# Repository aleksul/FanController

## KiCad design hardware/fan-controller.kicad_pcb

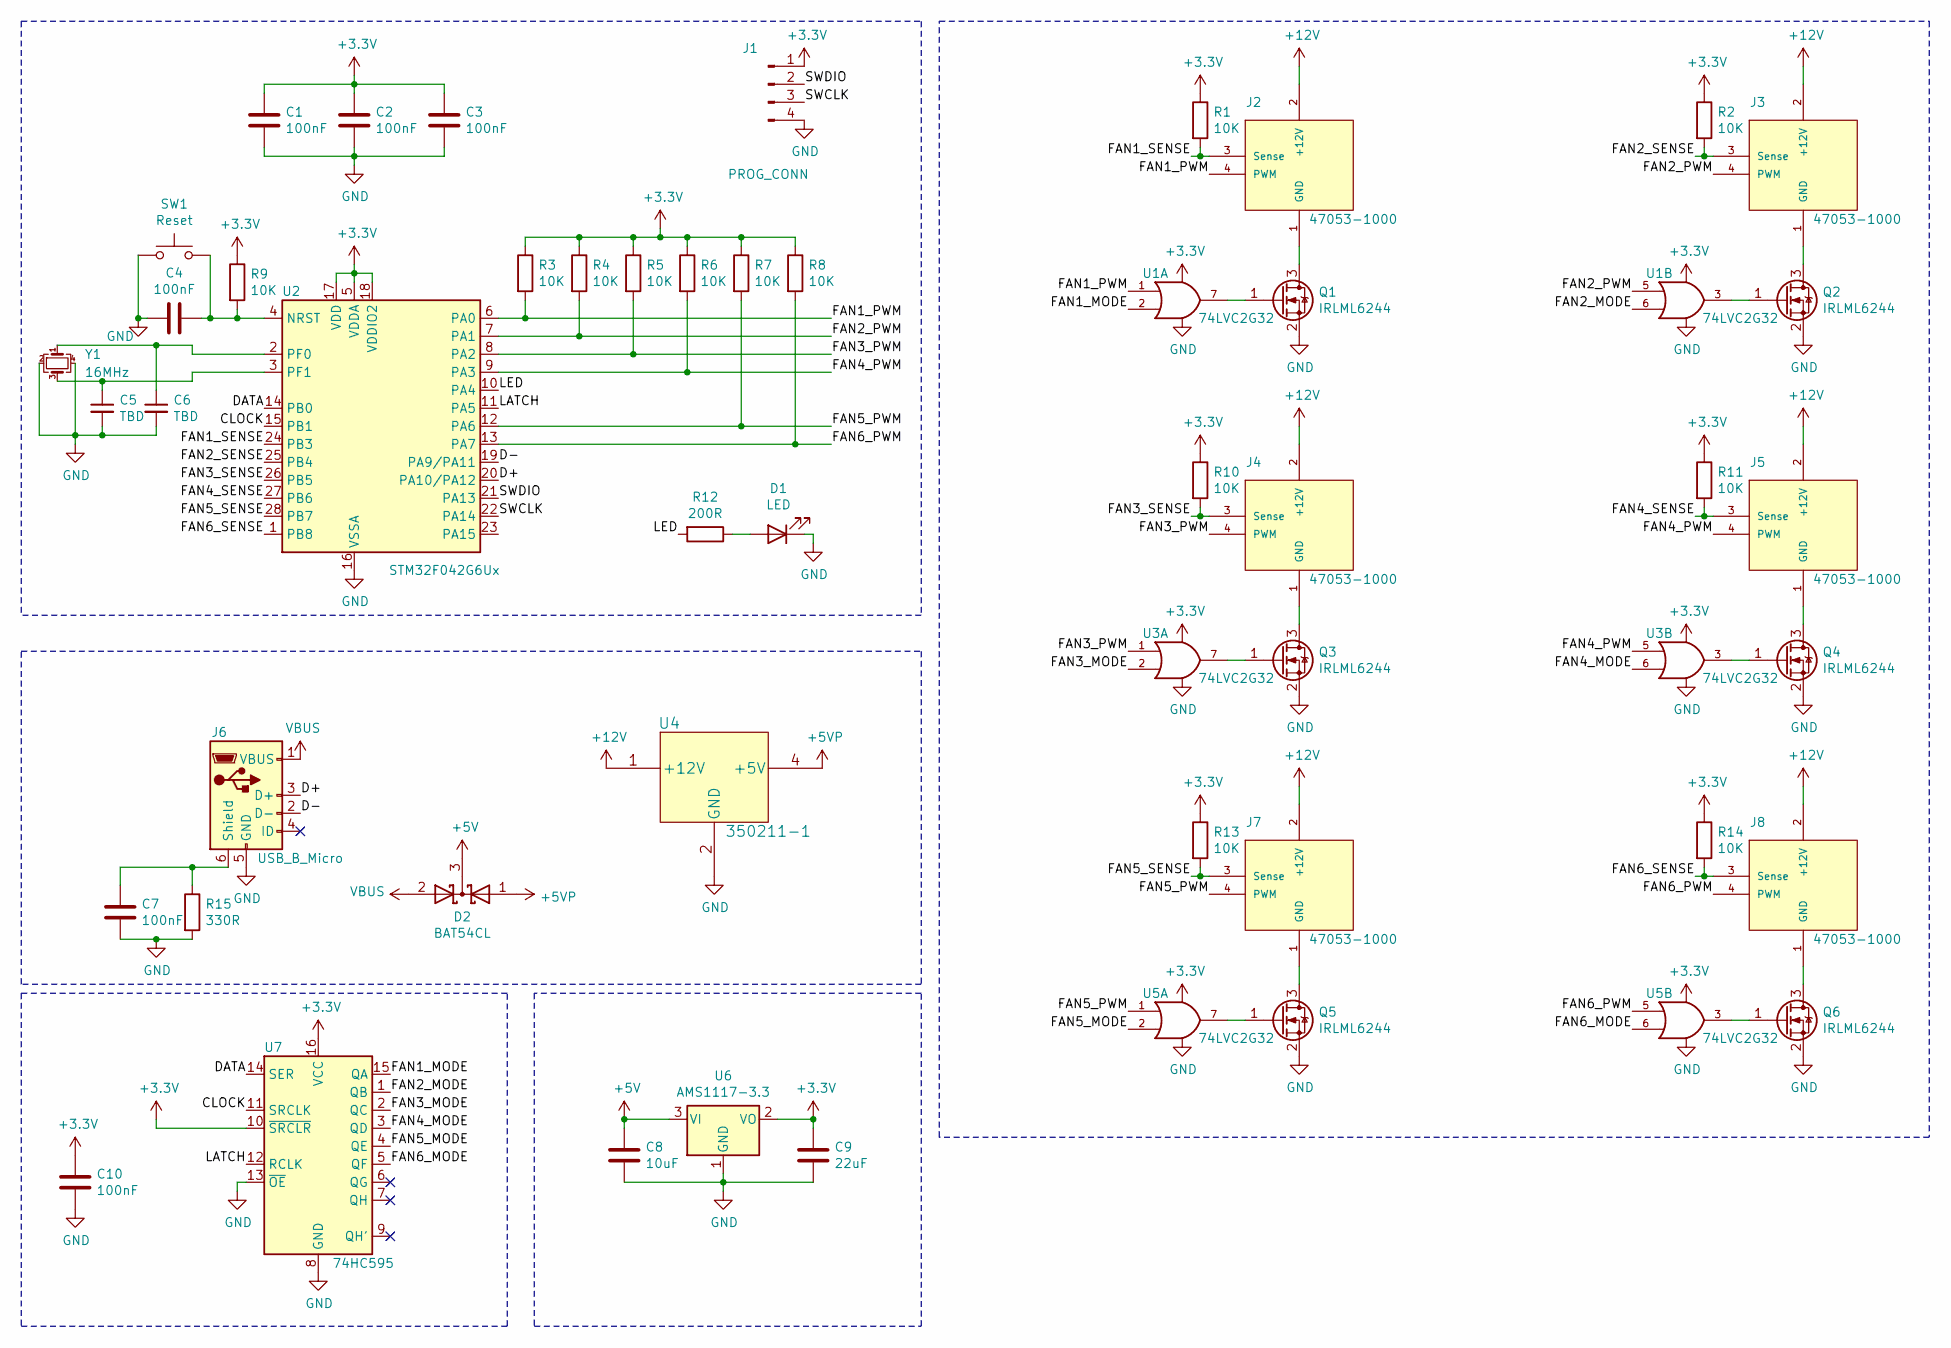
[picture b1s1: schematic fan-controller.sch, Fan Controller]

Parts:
C1, C2, C3, C4, C7, C10: 100nF; C_0805_2012Metric_Pad1.18x1.45mm_HandSolder
C5, C6: TBD; C_0805_2012Metric_Pad1.18x1.45mm_HandSolder
C8: 10uF; C_1206_3216Metric_Pad1.33x1.80mm_HandSolder
C9: 22uF; C_1206_3216Metric_Pad1.33x1.80mm_HandSolder
D1: LED; LED_1206_3216Metric_Pad1.42x1.75mm_HandSolder
D2: BAT54CL; SOT-23_Handsoldering
J1: PROG_CONN; PinHeader_1x04_P2.54mm_Vertical
J2, J3, J4, J5, J7, J8: 47053-1000; 470531000
J6: USB_B_Micro; USB_Micro-B_Molex-105017-0001
Q1, Q2, Q3, Q4, Q5, Q6: IRLML6244; SOT-23_Handsoldering
R1, R2, R3, R4, R5, R6, R7, R8, R9, R10, R11, R13, R14: 10K; R_0805_2012Metric_Pad1.20x1.40mm_HandSolder
R12: 200R; R_0805_2012Metric_Pad1.20x1.40mm_HandSolder
R15: 330R; R_0805_2012Metric_Pad1.20x1.40mm_HandSolder
SW1: Reset; SW_TS-1187A-B-A-B
U1, U3, U5: 74LVC2G32; VSSOP-8_2.3x2mm_P0.5mm
U2: STM32F042G6Ux; QFN-28_4x4mm_P0.5mm
U4: 350211-1
U6: AMS1117-3.3; SOT-223-3_TabPin2
U7: 74HC595; SOIC-16_3.9x9.9mm_P1.27mm
Y1: 16MHz; Crystal_SMD_2520-4Pin_2.5x2.0mm

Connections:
+3V3: C1.1, C2.1, C3.1, C9.1, C10.1, J1.1, R1.1, R2.1, R3.1, R4.1, R5.1, R6.1, R7.1, R8.1, R9.1, R10.1, R11.1, R13.1, R14.1, U1.8 (VCC), U2.5 (VDDA), U2.17 (VDD), U2.18 (VDDIO2), U3.8 (VCC), U5.8 (VCC), U6.2 (VO), U7.10 (~SRCLR), U7.16 (VCC)
+5V: C8.1, D2.3 (K), U6.3 (VI)
+5VP: D2.1 (A), U4.4 (+5V)
+12V: J2.2 (+12V), J3.2 (+12V), J4.2 (+12V), J5.2 (+12V), J7.2 (+12V), J8.2 (+12V), U4.1 (+12V)
/CLOCK: U2.15 (PB1), U7.11 (SRCLK)
/D+: J6.3 (D+), U2.20 (PA10/PA12)
/D-: J6.2 (D-), U2.19 (PA9/PA11)
/DATA: U2.14 (PB0), U7.14 (SER)
/FAN1_MODE: U1.2, U7.15 (QA)
/FAN1_PWM: J2.4 (PWM), R3.2, U1.1, U2.6 (PA0)
/FAN1_SENSE: J2.3 (Sense), R1.2, U2.24 (PB3)
/FAN2_MODE: U1.6, U7.1 (QB)
/FAN2_PWM: J3.4 (PWM), R4.2, U1.5, U2.7 (PA1)
/FAN2_SENSE: J3.3 (Sense), R2.2, U2.25 (PB4)
/FAN3_MODE: U3.2, U7.2 (QC)
/FAN3_PWM: J4.4 (PWM), R5.2, U2.8 (PA2), U3.1
/FAN3_SENSE: J4.3 (Sense), R10.2, U2.26 (PB5)
/FAN4_MODE: U3.6, U7.3 (QD)
/FAN4_PWM: J5.4 (PWM), R6.2, U2.9 (PA3), U3.5
/FAN4_SENSE: J5.3 (Sense), R11.2, U2.27 (PB6)
/FAN5_MODE: U5.2, U7.4 (QE)
/FAN5_PWM: J7.4 (PWM), R7.2, U2.12 (PA6), U5.1
/FAN5_SENSE: J7.3 (Sense), R13.2, U2.28 (PB7)
/FAN6_MODE: U5.6, U7.5 (QF)
/FAN6_PWM: J8.4 (PWM), R8.2, U2.13 (PA7), U5.5
/FAN6_SENSE: J8.3 (Sense), R14.2, U2.1 (PB8)
/LATCH: U2.11 (PA5), U7.12 (RCLK)
/LED: R12.2, U2.10 (PA4)
/SWCLK: J1.3, U2.22 (PA14)
/SWDIO: J1.2, U2.21 (PA13)
GND: C1.2, C2.2, C3.2, C4.2, C5.2, C6.2, C7.2, C8.2, C9.2, C10.2, D1.1 (K), J1.4, J6.5 (GND), Q1.2 (S), Q2.2 (S), Q3.2 (S), Q4.2 (S), Q5.2 (S), Q6.2 (S), R15.2, SW1.1, U1.4 (GND), U2.16 (VSSA), U3.4 (GND), U4.2 (GND), U4.3 (GND), U5.4 (GND), U6.1 (GND), U7.8 (GND), U7.13 (~OE), Y1.2, Y1.4
unnamed: C4.1, R9.2, SW1.2, U2.4 (NRST)
unnamed: C5.1, U2.3 (PF1), Y1.3
unnamed: C6.1, U2.2 (PF0), Y1.1
unnamed: C7.1, J6.6 (Shield), R15.1
unnamed: D1.2 (A), R12.1
unnamed: J2.1 (GND), Q1.3 (D)
unnamed: J3.1 (GND), Q2.3 (D)
unnamed: J4.1 (GND), Q3.3 (D)
unnamed: J5.1 (GND), Q4.3 (D)
unnamed: J7.1 (GND), Q5.3 (D)
unnamed: J8.1 (GND), Q6.3 (D)
unnamed: Q1.1 (G), U1.7
unnamed: Q2.1 (G), U1.3
unnamed: Q3.1 (G), U3.7
unnamed: Q4.1 (G), U3.3
unnamed: Q5.1 (G), U5.7
unnamed: Q6.1 (G), U5.3
VBUS: D2.2 (A), J6.1 (VBUS)

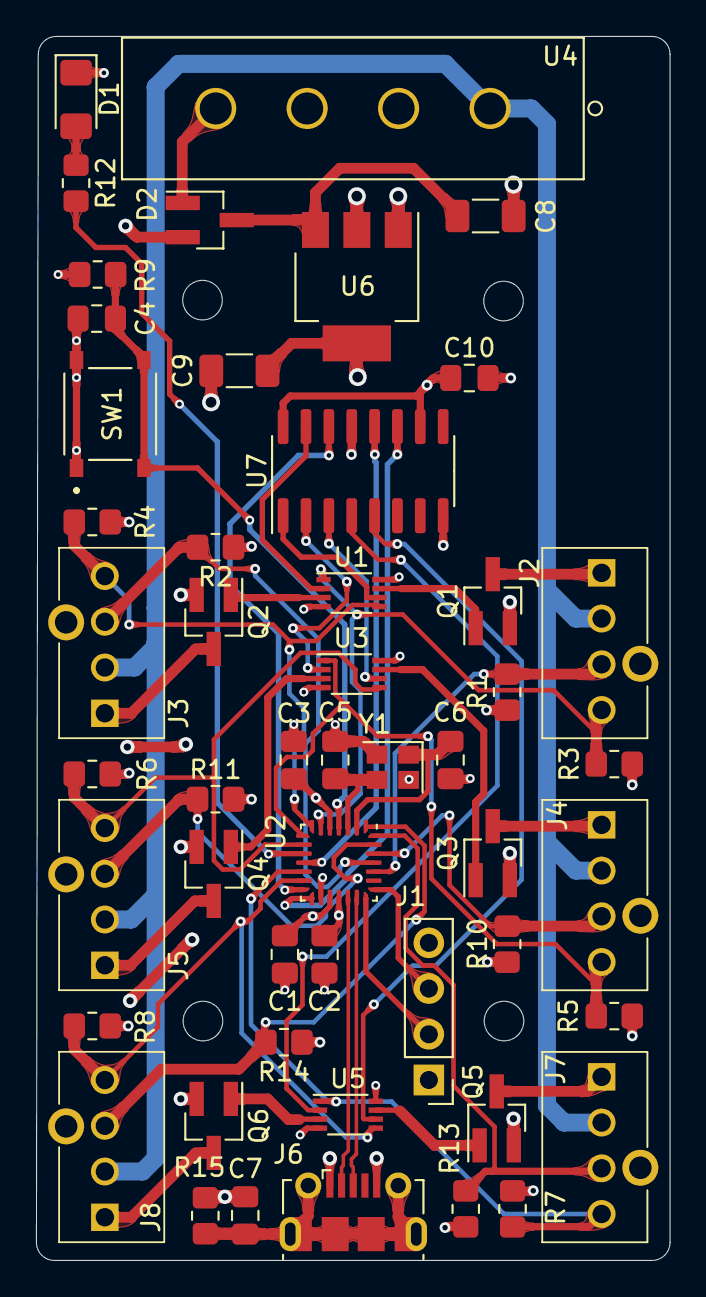
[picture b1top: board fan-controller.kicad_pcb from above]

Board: 4 copper layers, 35.2 x 68.0 mm, 54 parts (0 on the bottom side), 49 nets.

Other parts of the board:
M1, M2, M3, M4: MountingHole_2.2mm_M2

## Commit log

2021-06-05 Add schematic
2021-06-07 Done PCB, changed schematic a bit
